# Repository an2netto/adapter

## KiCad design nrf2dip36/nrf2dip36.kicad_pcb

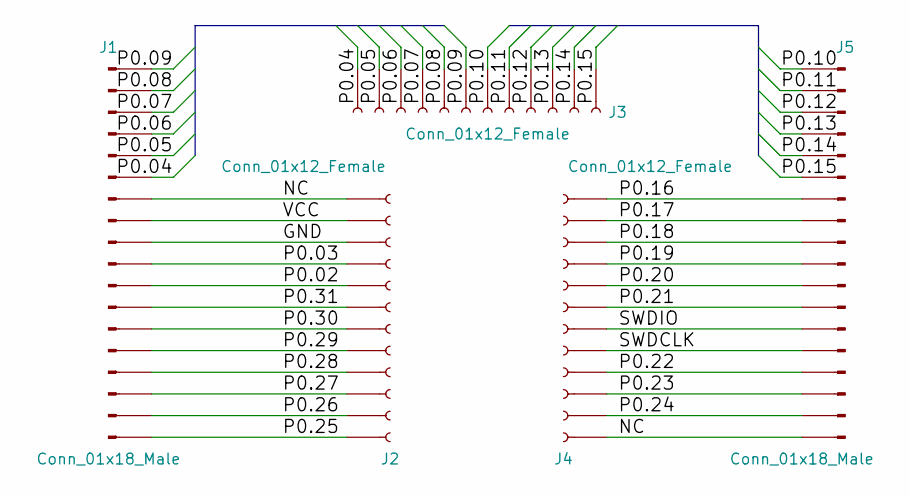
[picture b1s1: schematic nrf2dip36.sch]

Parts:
J1, J5: Conn_01x18_Male
J2, J3, J4: Conn_01x12_Female

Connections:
/GND: J1.9, J2.3
/NC: J1.7, J2.1, J4.1, J5.1
/P0.02: J1.11, J2.5
/P0.03: J1.10, J2.4
/P0.04: J1.6, J3.12
/P0.05: J1.5, J3.11
/P0.06: J1.4, J3.10
/P0.07: J1.3, J3.9
/P0.08: J1.2, J3.8
/P0.09: J1.1, J3.7
/P0.10: J3.6, J5.18
/P0.11: J3.5, J5.17
/P0.12: J3.4, J5.16
/P0.13: J3.3, J5.15
/P0.14: J3.2, J5.14
/P0.15: J3.1, J5.13
/P0.16: J4.12, J5.12
/P0.17: J4.11, J5.11
/P0.18: J4.10, J5.10
/P0.19: J4.9, J5.9
/P0.20: J4.8, J5.8
/P0.21: J4.7, J5.7
/P0.22: J4.4, J5.4
/P0.23: J4.3, J5.3
/P0.24: J4.2, J5.2
/P0.25: J1.18, J2.12
/P0.26: J1.17, J2.11
/P0.27: J1.16, J2.10
/P0.28: J1.15, J2.9
/P0.29: J1.14, J2.8
/P0.30: J1.13, J2.7
/P0.31: J1.12, J2.6
/SWDCLK: J4.5, J5.5
/SWDIO: J4.6, J5.6
/VCC: J1.8, J2.2

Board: 2 copper layers, 5 parts (0 on the bottom side), 35 nets, no tracks yet.

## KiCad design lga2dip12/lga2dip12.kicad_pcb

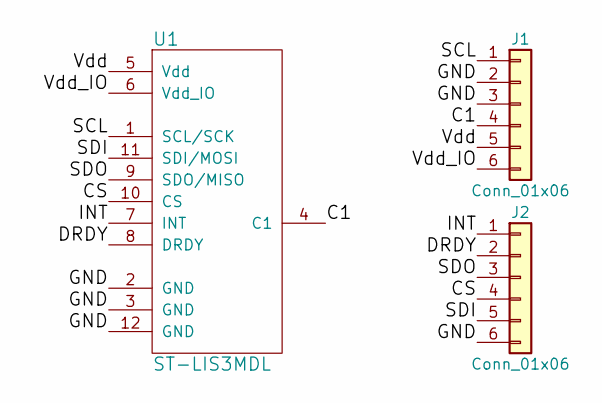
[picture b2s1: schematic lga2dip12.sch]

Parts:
J1, J2: Conn_01x06; Pin_Header_Straight_1x06_Pitch2.54mm
U1: ST-LIS3MDL; LGA-12

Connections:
/C1: J1.4, U1.4 (C1)
/CS: J2.4, U1.10 (CS)
/DRDY: J2.2, U1.8 (DRDY)
/GND: J1.2, J1.3, J2.6, U1.2 (GND), U1.3 (GND), U1.12 (GND)
/INT: J2.1, U1.7 (INT)
/SCL: J1.1, U1.1 (SCL/SCK)
/SDI: J2.5, U1.11 (SDI/MOSI)
/SDO: J2.3, U1.9 (SDO/MISO)
/Vdd: J1.5, U1.5 (Vdd)
/Vdd_IO: J1.6, U1.6 (Vdd_IO)

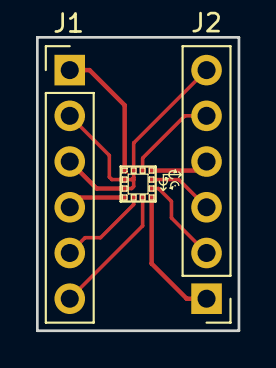
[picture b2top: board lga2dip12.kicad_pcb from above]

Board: 2 copper layers, 11.2 x 16.3 mm, 3 parts (0 on the bottom side), 10 nets.
